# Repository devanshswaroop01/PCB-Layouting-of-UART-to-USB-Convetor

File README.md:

# USB-to-UART Converter PCB Design using KiCad 9

<div align="left">

**A compact two-layer USB-to-UART converter PCB designed from schematic capture to fabrication-ready manufacturing files using KiCad 9.**

</div>

---

# Project Overview

Modern computers primarily communicate using **USB**, while many embedded systems, microcontrollers, and development boards communicate using **UART (Universal Asynchronous Receiver Transmitter)**. Since these two communication protocols are not directly compatible, a USB-to-UART bridge is required.

This project presents the complete hardware design of a **USB-to-UART Converter PCB** developed entirely in **KiCad 9**. The design converts USB communication into UART signals using the **Silicon Labs CP2102N USB-to-UART Bridge Controller**, enabling reliable serial communication between a host computer and external embedded systems.

The project demonstrates the complete PCB development lifecycle, including:

- Requirement Analysis
- Schematic Design
- PCB Layout
- Component Placement
- Manual Routing
- Ground Plane Implementation
- ERC & DRC Verification
- Gerber Generation
- Drill File Generation
- Technical Documentation

---

# Why this Project?

Many embedded development boards expose only UART communication.

Examples include:

- STM32 Boards
- AVR Microcontrollers
- PIC Microcontrollers
- ESP32
- 8051 Development Boards
- FPGA Development Boards
- Custom Embedded Hardware

Since modern laptops generally provide USB ports instead of UART ports, a USB-to-UART converter is commonly used for:

- Firmware Uploading
- Serial Debugging
- Bootloader Programming
- Embedded Development
- Device Configuration
- Industrial Communication

This project implements that interface in the form of a compact two-layer PCB.

---

# Project Objectives

The objectives of this project were to:

- Design a complete USB-to-UART converter schematic.
- Develop a compact two-layer PCB.
- Implement efficient component placement.
- Perform manual PCB routing.
- Implement proper power distribution.
- Generate fabrication-ready manufacturing files.
- Verify the design using ERC and DRC.
- Produce complete engineering documentation.

---

# System Architecture

```
                 Host Computer
                       │
                 USB Type-C Cable
                       │
                       ▼
              USB Type-C Connector
                       │
                       ▼
              USB Protection Circuit
          (ESD Protection + CC Resistors)
                       │
                       ▼
               Power Distribution
             (VBUS + Decoupling Network)
                       │
                       ▼
             CP2102N USB-UART Bridge
                       │
          ┌────────────┴────────────┐
          │                         │
         TX                        RX
          │                         │
          └────────────┬────────────┘
                       ▼
                UART Output Header
         GND | VBUS | RX | TX | RST
```

---

# Hardware Features

- USB Type-C Interface
- CP2102N USB-to-UART Bridge
- UART Communication
- Reset Pin
- TX/RX Status LEDs
- USB ESD Protection
- CC Pull-Down Configuration
- Decoupling Capacitors
- Two-Layer PCB
- Compact PCB Layout
- Ground Plane Implementation

---

# Major Hardware Components

| Component | Purpose |
|------------|----------|
| USB Type-C Connector | USB Interface |
| CP2102N | USB-to-UART Protocol Conversion |
| CC Resistors | USB Type-C Configuration |
| ESD Protection Diodes | USB Protection |
| Decoupling Capacitors | Power Filtering |
| TX/RX LEDs | Communication Status |
| UART Header | External UART Interface |

---

# PCB Design Flow

```
Requirements Analysis
        │
        ▼
Component Selection
        │
        ▼
Schematic Design
        │
        ▼
Footprint Assignment
        │
        ▼
ERC Verification
        │
        ▼
PCB Layout
        │
        ▼
Component Placement
        │
        ▼
Manual Routing
        │
        ▼
Ground Plane
        │
        ▼
DRC Verification
        │
        ▼
Gerber Generation
        │
        ▼
Drill File Generation
        │
        ▼
Project Documentation
```

---

# Design Highlights

### Schematic Design

- Complete circuit designed from scratch.
- USB interface implementation.
- Power network design.
- UART interface.
- LED indicators.
- USB protection circuitry.

---

### PCB Layout

- Two-layer PCB.
- Compact board size.
- Manual routing.
- Optimized signal flow.
- Organized component placement.
- Ground plane implementation.

---

### Routing Strategy

- Short signal paths.
- Reduced routing congestion.
- Logical component grouping.
- Efficient via usage.
- Clean power routing.

---

### Verification

Electrical verification was performed using KiCad.

✔ Electrical Rules Check (ERC)

✔ Design Rules Check (DRC)

---

### Manufacturing Outputs

Fabrication files generated include:

- Gerber Files
- Drill Files
- PCB Layout
- Native KiCad Project
- Verification Reports

---

# Repository Structure

```
USB-to-UART-Converter/

│
├── README.md
│
├── Project/
│   ├── USB_to_UART.kicad_pro
│   ├── USB_to_UART.kicad_sch
│   ├── USB_to_UART.kicad_pcb
│
├── Gerber/
│   ├── F_Cu.gbr
│   ├── B_Cu.gbr
│   ├── F_Mask.gbr
│   ├── B_Mask.gbr
│   ├── F_Silkscreen.gbr
│   ├── Edge_Cuts.gbr
│
├── Drill/
│   ├── USB_to_UART-PTH.drl
│   ├── USB_to_UART-NPTH.drl
│
├── Reports/
│   ├── PCB_Design_Report.pdf
│   ├── Gerber_Report.pdf
│   ├── Drill_Report.pdf
│   ├── ERC_DRC_Report.pdf
│
├── Images/
│   ├── Schematic.png
│   ├── PCB_Layout.png
│   ├── PCB_3D_Front.png
│   ├── PCB_3D_Back.png
│
└── Verification/
    ├── ERC.rpt
    └── DRC.rpt
```

---

# Verification Summary

| Verification | Status |
|--------------|--------|
| ERC Completed | ✅ |
| DRC Completed | ✅ |
| PCB Routing | ✅ |
| Ground Plane | ✅ |
| Gerber Generation | ✅ |
| Drill File Generation | ✅ |

---

# Engineering Skills Demonstrated

This project demonstrates practical experience in:

- Electronic Schematic Design
- PCB Design using KiCad 9
- Footprint Management
- Component Placement
- PCB Routing
- Ground Plane Design
- Power Distribution
- USB Hardware Design
- UART Communication
- PCB Verification
- Gerber Generation
- Drill File Generation
- Technical Documentation

---

# What I Learned

Through this project I gained practical experience in:

- Designing a complete PCB from schematic to fabrication.
- Selecting electronic components and footprints.
- Planning efficient PCB layouts.
- Implementing proper grounding techniques.
- Generating manufacturing files.
- Performing electrical and layout verification.
- Preparing engineering documentation for hardware projects.

---

# Future Improvements

Potential future enhancements include:

- Hardware testing and validation on a fabricated PCB.
- Additional ESD protection.
- Test points for debugging.
- Power status LED.
- Improved silkscreen annotations.
- Version 2.0 PCB optimization.

---

# Software Used

- KiCad 9
- KiCad PCB Editor
- KiCad Schematic Editor
- KiCad 3D Viewer

---

# Applications

This PCB can be used for:

- Embedded Systems Development
- Firmware Programming
- Serial Debugging
- Bootloader Programming
- FPGA Communication
- IoT Development
- Industrial Automation
- Educational Laboratories

---

# Project Status

| Stage | Status |
|---------|--------|
| Requirements | ✅ Complete |
| Schematic Design | ✅ Complete |
| PCB Layout | ✅ Complete |
| Routing | ✅ Complete |
| ERC | ✅ Complete |
| DRC | ✅ Complete |
| Gerber Generation | ✅ Complete |
| Drill Files | ✅ Complete |
| Documentation | ✅ Complete |
| Project | ✅ Finalized |
---

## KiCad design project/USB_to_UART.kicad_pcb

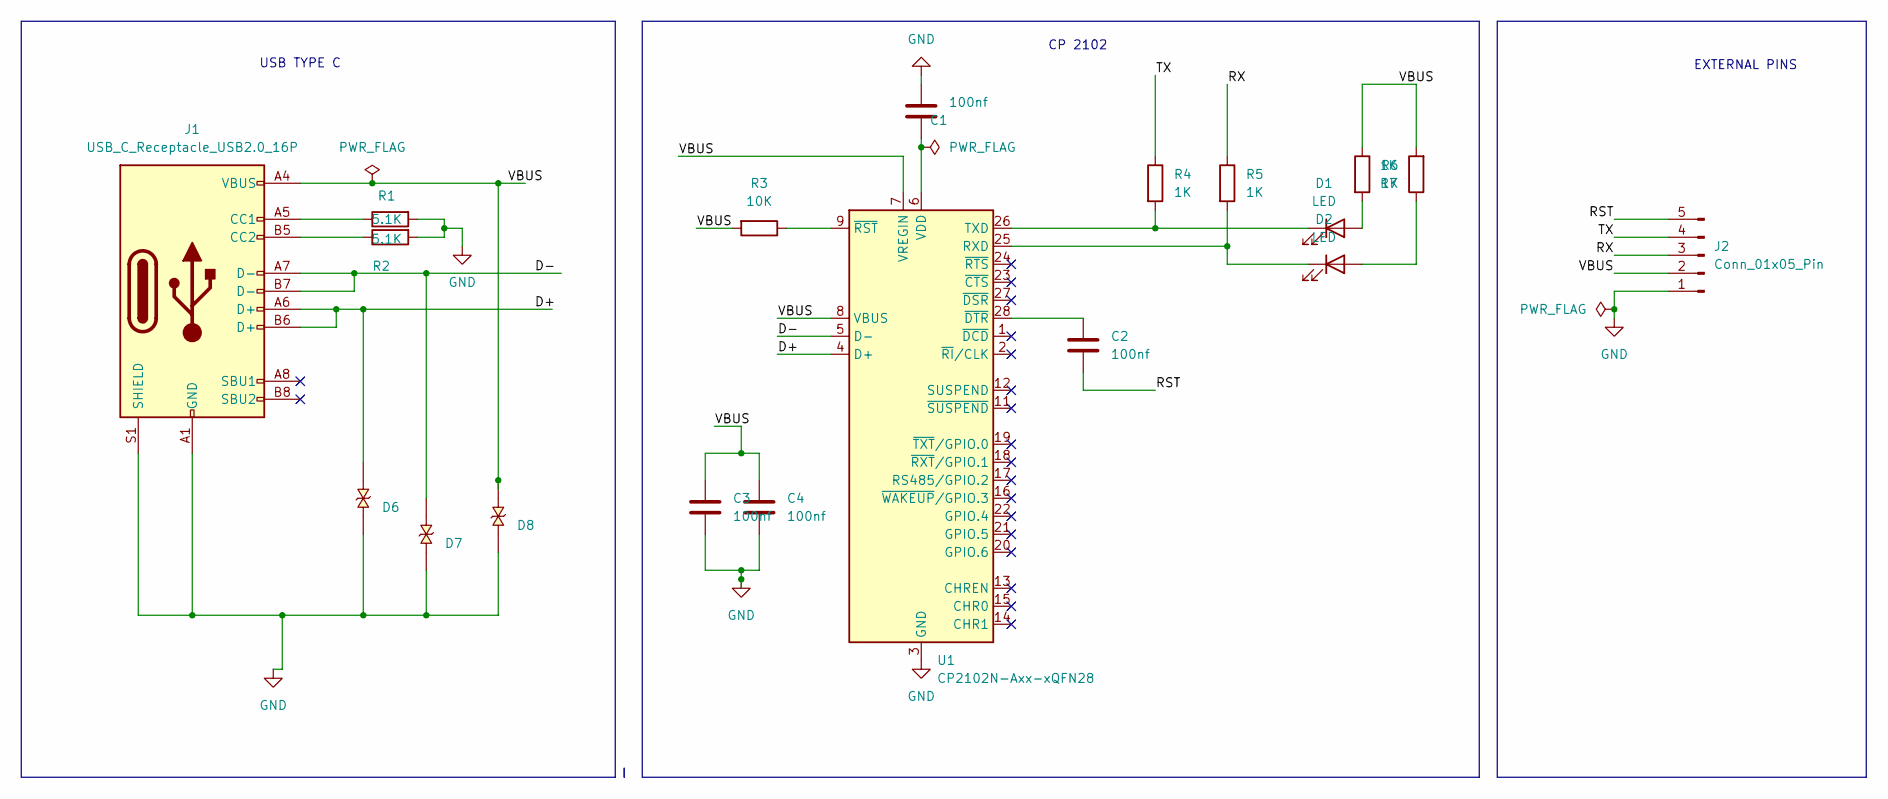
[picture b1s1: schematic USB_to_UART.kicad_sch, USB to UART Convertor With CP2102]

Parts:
C1, C2, C3, C4: 100nf; C_0201_0603Metric
D1, D2: LED; LED_0201_0603Metric
D6, D7, D8: LESD5D5.0CT1G; TVS_LESD5D5.0CT1G; PARTREV O
J1: USB_C_Receptacle_USB2.0_16P; USB_C_Receptacle_HRO_TYPE-C-31-M-12
J2: Conn_01x05_Pin; PinHeader_1x05_P2.54mm_Horizontal
R1, R2: 5.1K; R_0201_0603Metric
R3: 10K; R_0201_0603Metric
R4, R6, R7: 1K; R_0201_0603Metric
R5: 1K; R_0603_1608Metric
U1: CP2102N-Axx-xQFN28; QFN-28-1EP_5x5mm_P0.5mm_EP3.35x3.35mm

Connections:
/D+: D6.2, J1.A6 (D+), J1.B6 (D+), U1.4 (D+)
/D-: D7.2, J1.A7 (D-), J1.B7 (D-), U1.5 (D-)
/RST: C2.2, J2.5
/RX: J2.3, R5.1
/TX: J2.4, R4.1
/VBUS: C3.1, C4.1, D8.2, J1.A4 (VBUS), J1.A9 (VBUS), J1.B4 (VBUS), J1.B9 (VBUS), J2.2, R3.2, R6.1, R7.2, U1.7 (VREGIN), U1.8 (VBUS)
GND: C1.2, C3.2, C4.2, D6.1, D7.1, D8.1, J1.A1 (GND), J1.A12 (GND), J1.B1 (GND), J1.B12 (GND), J1.S1 (SHIELD), J2.1, R1.2, R2.2, U1.3 (GND), U1.29 (GND)
unnamed: D1.2 (A), R6.2
unnamed: D1.1 (K), R4.2, U1.26 (TXD)
unnamed: D2.2 (A), R7.1
unnamed: D2.1 (K), R5.2, U1.25 (RXD)
unnamed: J1.A5 (CC1), R1.1
unnamed: J1.B5 (CC2), R2.1
unnamed: C1.1, U1.6 (VDD)
unnamed: C2.1, U1.28 (~DTR)
unnamed: R3.1, U1.9 (~RST)

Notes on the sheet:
CP 2102
USB TYPE C
EXTERNAL PINS

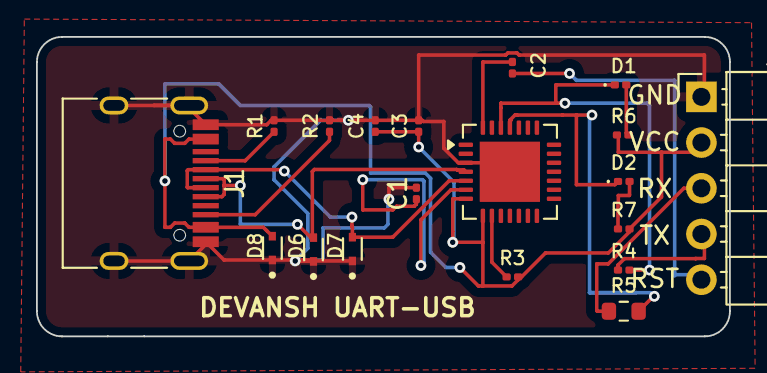
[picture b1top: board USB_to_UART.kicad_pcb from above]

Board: 2 copper layers, 38.5 x 16.6 mm, 19 parts (0 on the bottom side), 16 nets.

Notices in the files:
README.md:
License: MIT
